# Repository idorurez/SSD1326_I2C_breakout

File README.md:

# SSD1326 256x32 I2C oled breakout

## Features
* 5V+ in
* I2C
* Voltage regulator V3.3 out for logic
* Step up to 12V+ to power oled panel
* For use with ER-OLED01B-1 w/26 pin Ziff connector

## Notes
* `datasheet` folder includes datasheets for everything used here as well as ones I abandoned
* `onigaku` repo (not included in this repo) has all symbols and footprints are available

## Inspiration
* Adafruit schematics for latest SSD1306 breakout boards
* https://hackaday.io/project/173753-oled-breakout-board-with-dc-dc-step-up/details

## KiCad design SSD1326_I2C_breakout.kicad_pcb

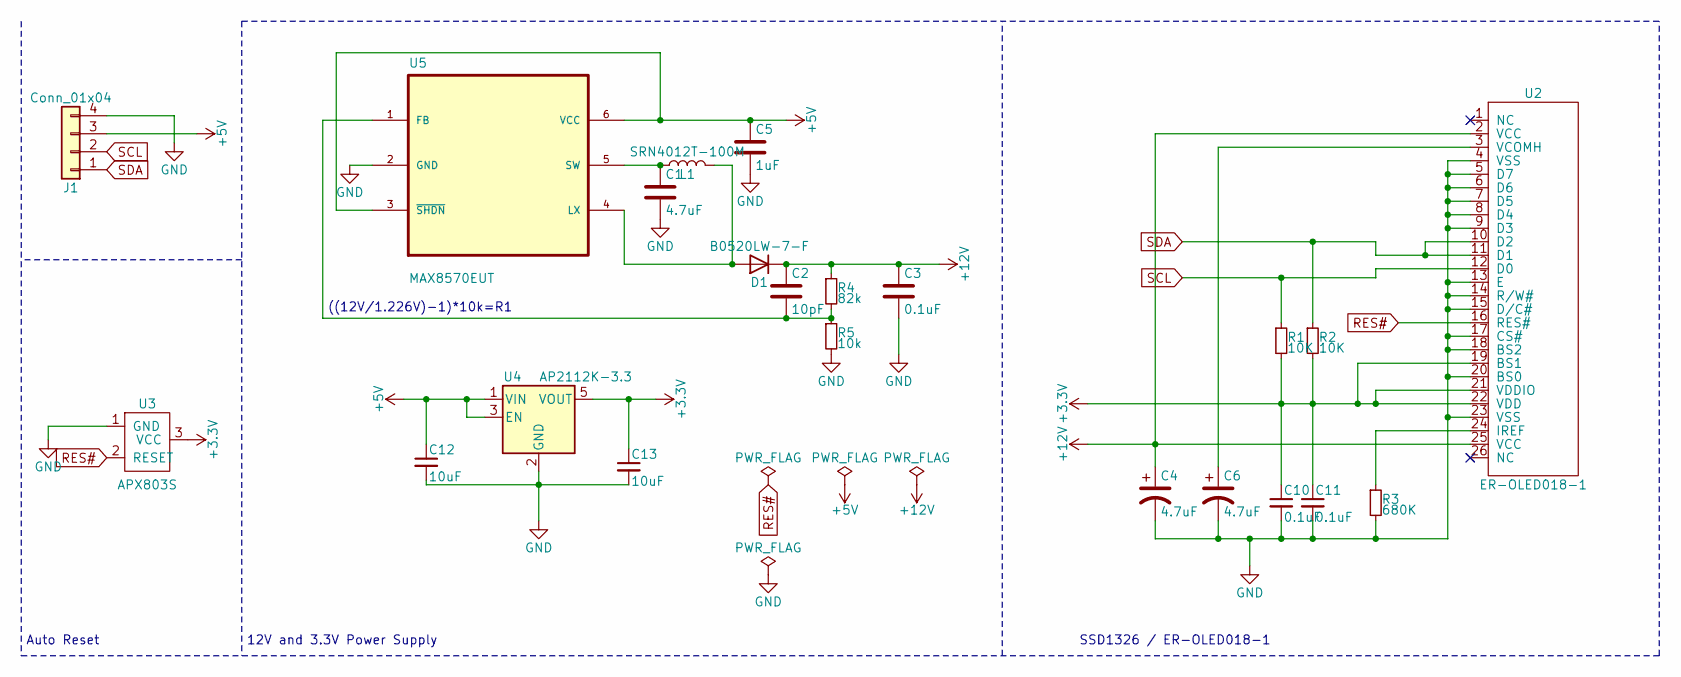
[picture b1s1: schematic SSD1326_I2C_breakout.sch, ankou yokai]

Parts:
C1: 4.7uF; C_0603_1608Metric_Pad1.08x0.95mm_HandSolder
C2: 10pF; C_0603_1608Metric_Pad1.08x0.95mm_HandSolder
C3, C10, C11: 0.1uF; C_0603_1608Metric_Pad1.08x0.95mm_HandSolder
C4, C6: 4.7uF; CP_EIA-2012-15_AVX-P_Pad1.30x1.05mm_HandSolder
C5: 1uF; C_0603_1608Metric_Pad1.08x0.95mm_HandSolder
C12, C13: 10uF; C_0603_1608Metric_Pad1.08x0.95mm_HandSolder
D1: ‎B0520LW-7-F‎; B0520LW
J1: Conn_01x04; OLED
L1: SRN4012T-100M
R1, R2: 10K; R_0603_1608Metric_Pad0.98x0.95mm_HandSolder
R3: 680K; R_0603_1608Metric_Pad0.98x0.95mm_HandSolder
R4: 82k; R_0603_1608Metric_Pad0.98x0.95mm_HandSolder
R5: 10k; R_0603_1608Metric_Pad0.98x0.95mm_HandSolder
U2: ER-OLED018-1; ER-CON26HT-1
U3: APX803S; APX803S-SA-SOT91P240X110-3N
U4: AP2112K-3.3; SOT-23-5
U5: MAX8570EUT; MAX8570EUT+SOT95P280X145-6N

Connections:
+3V3: C10.1, C11.1, C13.1, R1.2, R2.2, U2.19 (BS1), U2.21 (VDDIO), U2.22 (VDD), U3.3 (VCC), U4.5 (VOUT)
+5V: C5.1, C12.1, J1.3, U4.1 (VIN), U4.3 (EN), U5.3 (~SHDN), U5.6 (VCC); also elsewhere on the board
+12V: C2.1, C3.1, C4.1, D1.1 (K), R4.1, U2.2 (VCC), U2.25 (VCC)
GND: C1.2, C3.2, C4.2, C5.2, C6.2, C10.2, C11.2, C12.2, C13.2, J1.4, R3.2, R5.2, U2.4 (VSS), U2.5 (D7), U2.6 (D6), U2.7 (D5), U2.8 (D4), U2.9 (D3), U2.13 (E), U2.14 (R/W#), U2.15 (D/C#), U2.17 (CS#), U2.18 (BS2), U2.20 (BS0), U2.23 (VSS), U3.1 (GND), U4.2 (GND), U5.2 (GND); also elsewhere on the board
unnamed: C1.1, L1.1, U5.5 (SW)
unnamed: C2.2, R4.2, R5.1, U5.1 (FB)
unnamed: C6.1, U2.3 (VCOMH)
unnamed: D1.2 (A), L1.2, U5.4 (LX)
unnamed: R3.1, U2.24 (IREF)
RES#: U2.16 (RES#), U3.2 (RESET)
SCL: J1.2, R1.1, U2.12 (D0); also elsewhere on the board
SDA: J1.1, R2.1, U2.10 (D2), U2.11 (D1); also elsewhere on the board

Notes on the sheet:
12V and 3.3V Power Supply
Auto Reset
SSD1326 / ER-OLED018-1
((12V/1.226V)-1)*10k=R1

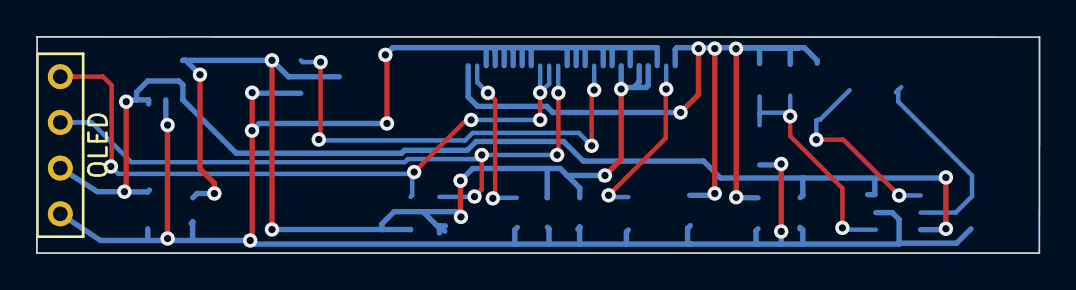
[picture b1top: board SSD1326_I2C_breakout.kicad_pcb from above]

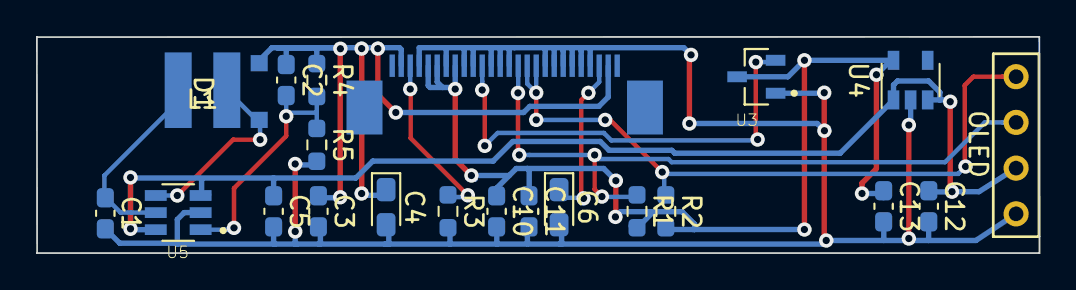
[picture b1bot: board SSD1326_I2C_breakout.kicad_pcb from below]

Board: 2 copper layers, 55.7 x 12.0 mm, 22 parts (21 on the bottom side), 12 nets.

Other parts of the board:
Jee: Conn_01x04; OLED

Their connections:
+5V: Jee.3; also elsewhere on the board
GND: Jee.4; also elsewhere on the board
SCL: Jee.2; also elsewhere on the board
SDA: Jee.1; also elsewhere on the board

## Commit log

2021-03-02 updated readme with some info
2021-03-02 initial add
2021-03-03 adding images and such
2021-03-04 swapped out max607 for a max8570 due to cost savings and obsoletion, using B0520LW schottky due to similar circumstances
2021-03-06 slimming down to 12mm
2021-03-06 udpated readme
2021-05-22 moved some stuff over
